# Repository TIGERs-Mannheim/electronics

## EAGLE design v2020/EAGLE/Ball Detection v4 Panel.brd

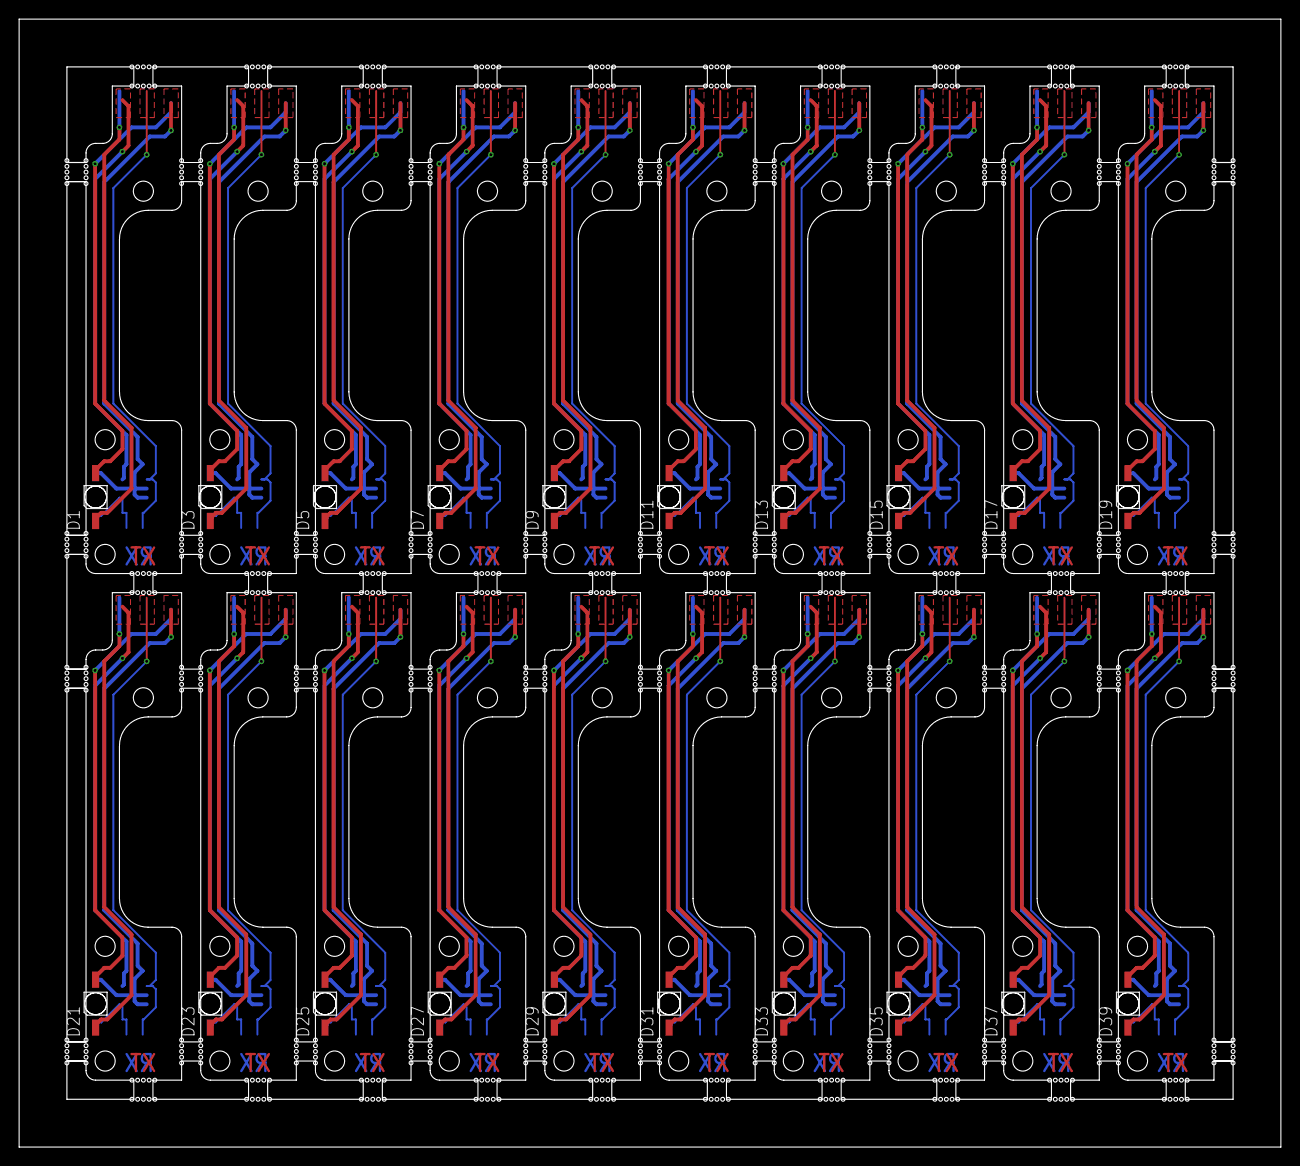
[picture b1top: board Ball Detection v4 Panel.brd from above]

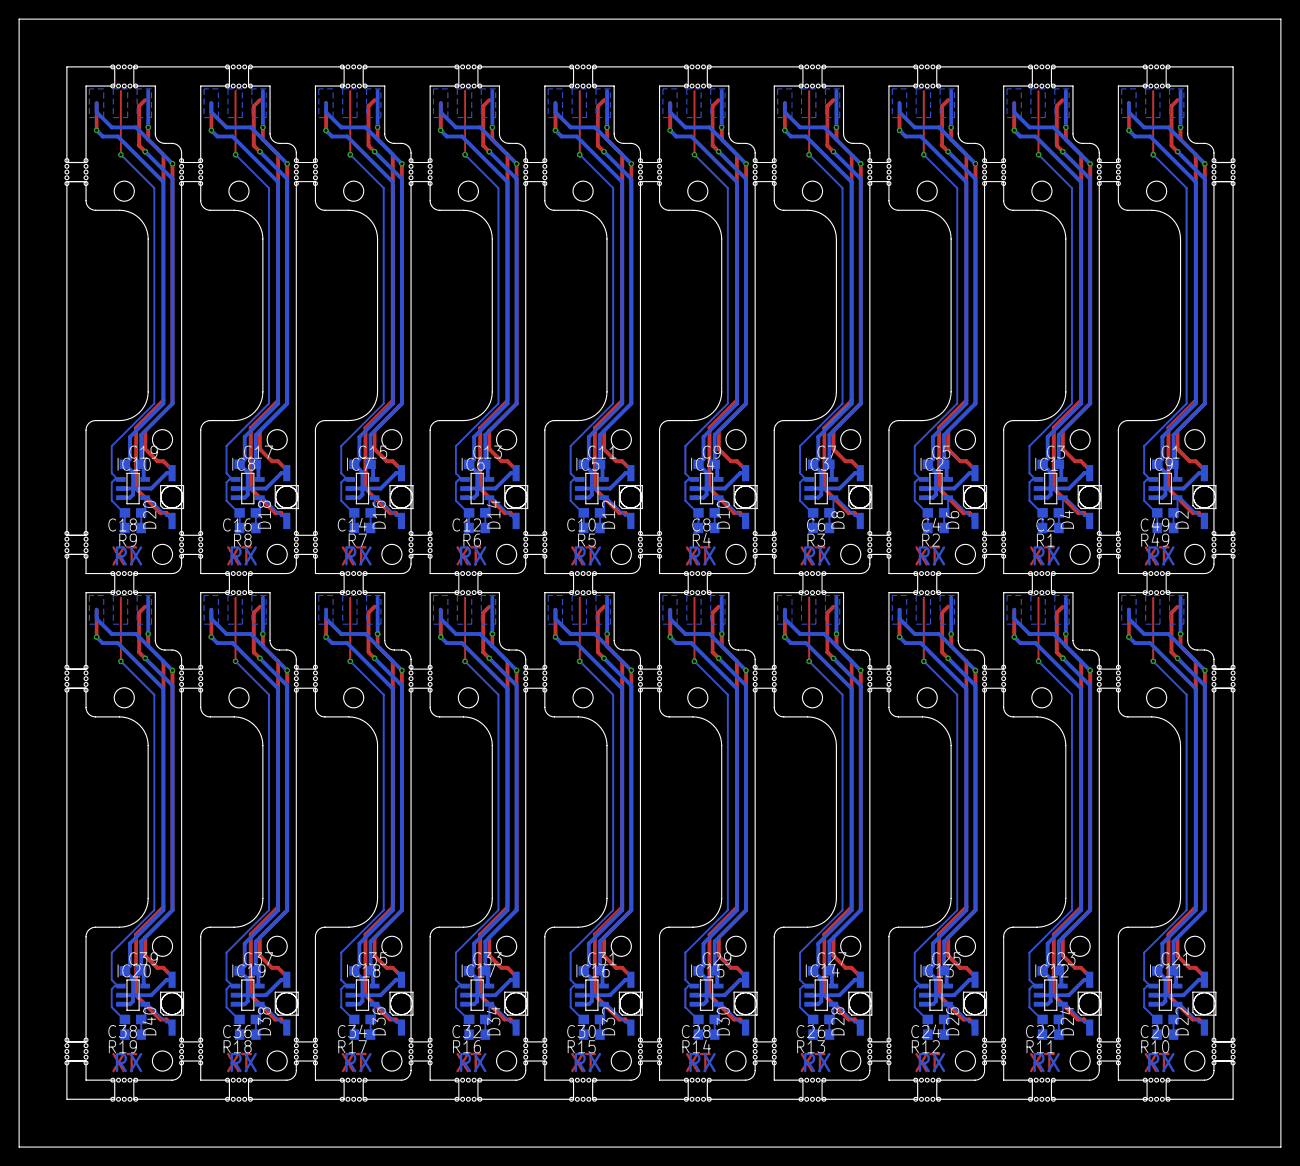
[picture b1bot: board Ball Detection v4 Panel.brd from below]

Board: 2 copper layers, 132.0 x 118.0 mm, 120 parts (100 on the bottom side), 80 nets.

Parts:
C1, C3, C5, C7, C9, C11, C13, C15, C17, C19, C21, C23, C25, C27, C29, C31, C33, C35, C37, C39: 10u; C0603
C2, C4, C6, C8, C10, C12, C14, C16, C18, C20, C22, C24, C26, C28, C30, C32, C34, C36, C38, C49: 10p; C0603
D1, D3, D5, D7, D9, D11, D13, D15, D17, D19, D21, D23, D25, D27, D29, D31, D33, D35, D37, D39: VSMB2000X01; LED-GULLR
D2, D4, D6, D8, D10, D12, D14, D16, D18, D20, D22, D24, D26, D28, D30, D32, D34, D36, D38, D40: TEMD1000; LED-GULLR
IC1, IC2, IC3, IC4, IC5, IC6, IC7, IC8, IC9, IC10, IC11, IC12, IC13, IC14, IC15, IC16, IC17, IC18, IC19, IC20: OPA320; SOT23-5
R1, R2, R3, R4, R5, R6, R7, R8, R9, R10, R11, R12, R13, R14, R15, R16, R17, R18, R19, R49: 1M; R0603

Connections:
GND: C1.1, D2.A, IC9.2, IC9.3
GND1: C3.1, D4.A, IC1.2, IC1.3
GND2: C5.1, D6.A, IC2.2, IC2.3
GND3: C7.1, D8.A, IC3.2, IC3.3
GND4: C9.1, D10.A, IC4.2, IC4.3
GND5: C11.1, D12.A, IC5.2, IC5.3
GND6: C13.1, D14.A, IC6.2, IC6.3
GND7: C15.1, D16.A, IC7.2, IC7.3
GND8: C17.1, D18.A, IC8.2, IC8.3
GND9: C19.1, D20.A, IC10.2, IC10.3
GND10: C21.1, D22.A, IC11.2, IC11.3
GND11: C23.1, D24.A, IC12.2, IC12.3
GND12: C25.1, D26.A, IC13.2, IC13.3
GND13: C27.1, D28.A, IC14.2, IC14.3
GND14: C29.1, D30.A, IC15.2, IC15.3
GND15: C31.1, D32.A, IC16.2, IC16.3
GND16: C33.1, D34.A, IC17.2, IC17.3
GND17: C35.1, D36.A, IC18.2, IC18.3
GND18: C37.1, D38.A, IC19.2, IC19.3
GND19: C39.1, D40.A, IC20.2, IC20.3
IR-ADC: C49.2, IC9.1, R49.2
IR-ADC1: C2.2, IC1.1, R1.2
IR-ADC2: C4.2, IC2.1, R2.2
IR-ADC3: C6.2, IC3.1, R3.2
IR-ADC4: C8.2, IC4.1, R4.2
IR-ADC5: C10.2, IC5.1, R5.2
IR-ADC6: C12.2, IC6.1, R6.2
IR-ADC7: C14.2, IC7.1, R7.2
IR-ADC8: C16.2, IC8.1, R8.2
IR-ADC9: C18.2, IC10.1, R9.2
IR-ADC10: C20.2, IC11.1, R10.2
IR-ADC11: C22.2, IC12.1, R11.2
IR-ADC12: C24.2, IC13.1, R12.2
IR-ADC13: C26.2, IC14.1, R13.2
IR-ADC14: C28.2, IC15.1, R14.2
IR-ADC15: C30.2, IC16.1, R15.2
IR-ADC16: C32.2, IC17.1, R16.2
IR-ADC17: C34.2, IC18.1, R17.2
IR-ADC18: C36.2, IC19.1, R18.2
IR-ADC19: C38.2, IC20.1, R19.2
unnamed: C2.1, D4.C, IC1.4, R1.1
unnamed: C4.1, D6.C, IC2.4, R2.1
unnamed: C6.1, D8.C, IC3.4, R3.1
unnamed: C8.1, D10.C, IC4.4, R4.1
unnamed: C10.1, D12.C, IC5.4, R5.1
unnamed: C12.1, D14.C, IC6.4, R6.1
unnamed: C14.1, D16.C, IC7.4, R7.1
unnamed: C16.1, D18.C, IC8.4, R8.1
unnamed: C18.1, D20.C, IC10.4, R9.1
unnamed: C20.1, D22.C, IC11.4, R10.1
unnamed: C22.1, D24.C, IC12.4, R11.1
unnamed: C24.1, D26.C, IC13.4, R12.1
unnamed: C26.1, D28.C, IC14.4, R13.1
unnamed: C28.1, D30.C, IC15.4, R14.1
unnamed: C30.1, D32.C, IC16.4, R15.1
unnamed: C32.1, D34.C, IC17.4, R16.1
unnamed: C34.1, D36.C, IC18.4, R17.1
unnamed: C36.1, D38.C, IC19.4, R18.1
unnamed: C38.1, D40.C, IC20.4, R19.1
unnamed: C49.1, D2.C, IC9.4, R49.1
RX+3V1: C3.2, IC1.5
RX+3V2: C5.2, IC2.5
RX+3V3: C1.2, IC9.5
RX+3V4: C7.2, IC3.5
RX+3V5: C9.2, IC4.5
RX+3V6: C11.2, IC5.5
RX+3V7: C13.2, IC6.5
RX+3V8: C15.2, IC7.5
RX+3V9: C17.2, IC8.5
RX+3V10: C19.2, IC10.5
RX+3V11: C21.2, IC11.5
RX+3V12: C23.2, IC12.5
RX+3V13: C25.2, IC13.5
RX+3V14: C27.2, IC14.5
RX+3V15: C29.2, IC15.5
RX+3V16: C31.2, IC16.5
RX+3V17: C33.2, IC17.5
RX+3V18: C35.2, IC18.5
RX+3V19: C37.2, IC19.5
RX+3V20: C39.2, IC20.5

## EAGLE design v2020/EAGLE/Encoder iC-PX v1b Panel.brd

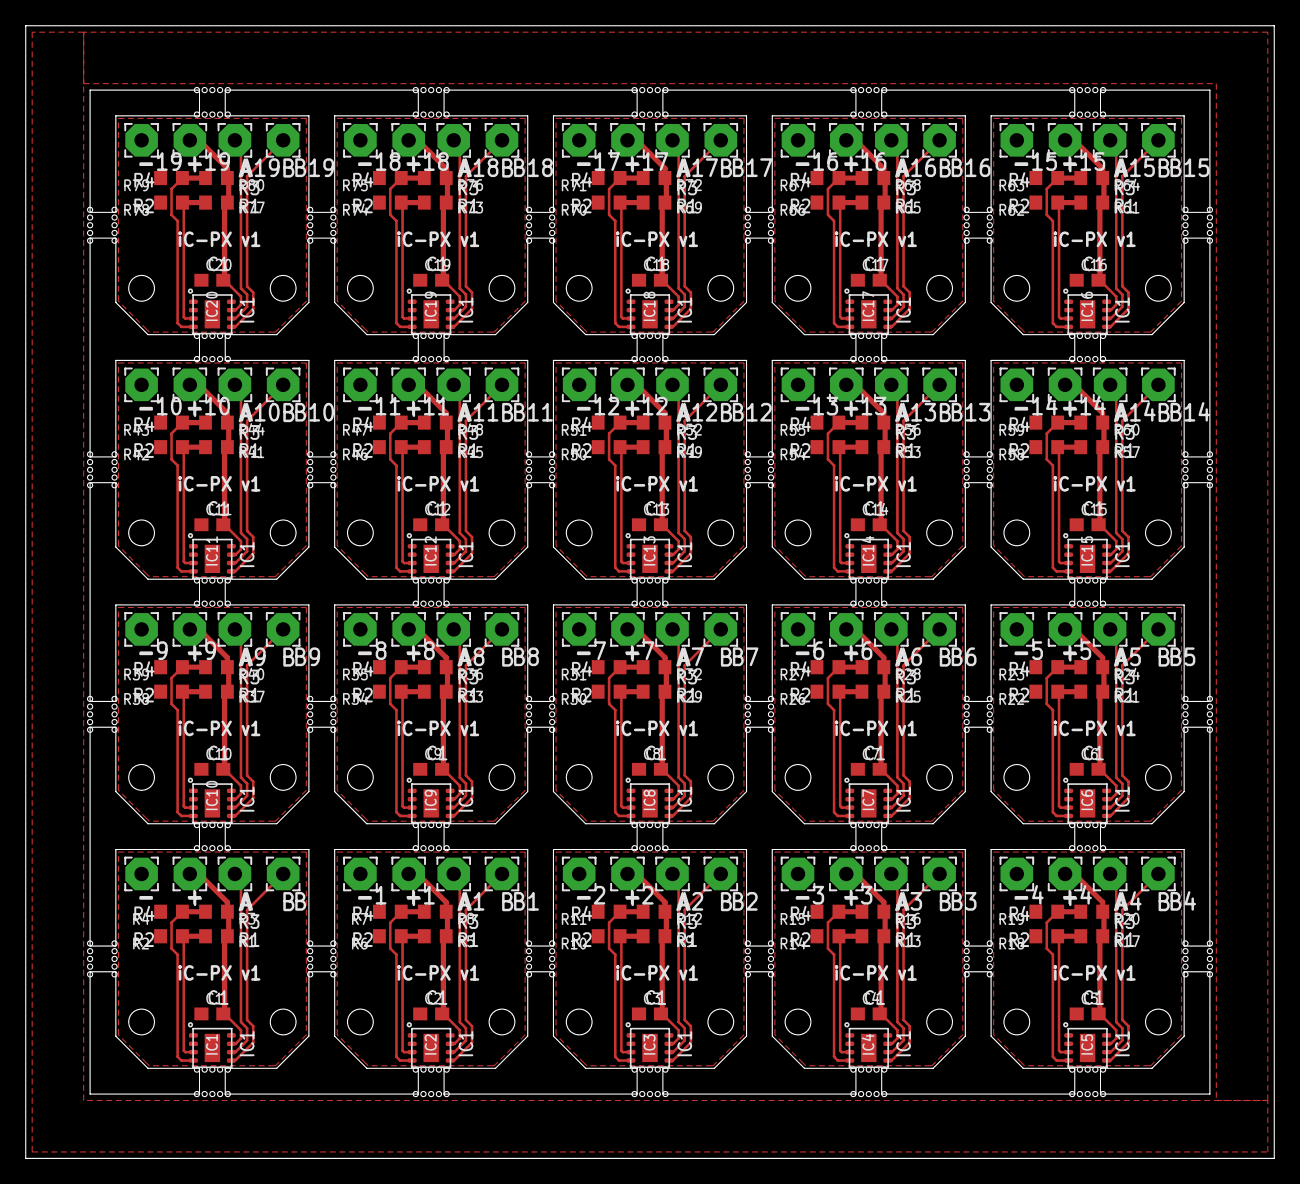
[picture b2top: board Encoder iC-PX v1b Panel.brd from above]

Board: 2 copper layers, 97.0 x 88.0 mm, 200 parts (0 on the bottom side), 120 nets.

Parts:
+, +1, +2, +3, +4, +5, +6, +7, +8, +9, +10, +11, +12, +13, +14, +15, +16, +17, +18, +19: WIREPAD2,54/1,1; 2,54/1,1
-, -1, -2, -3, -4, -5, -6, -7, -8, -9, -10, -11, -12, -13, -14, -15, -16, -17, -18, -19: WIREPAD2,54/1,1; 2,54/1,1
A, A1, A2, A3, A4, A5, A6, A7, A8, A9, A10, A11, A12, A13, A14, A15, A16, A17, A18, A19: WIREPAD2,54/1,1; 2,54/1,1
B, B1, B2, B3, B4, B5, B6, B7, B8, B9, B10, B11, B12, B13, B14, B15, B16, B17, B18, B19: WIREPAD2,54/1,1; 2,54/1,1
C1, C2, C3, C4, C5, C6, C7, C8, C9, C10, C11, C12, C13, C14, C15, C16, C17, C18, C19, C20: 100n; C0603
IC1, IC2, IC3, IC4, IC5, IC6, IC7, IC8, IC9, IC10, IC11, IC12, IC13, IC14, IC15, IC16, IC17, IC18, IC19, IC20: iC-PX2604; ODFN8-3X3
R1, R5, R9, R13, R17, R21, R25, R29, R33, R37, R41, R45, R49, R53, R57, R61, R65, R69, R73, R77: 0R; R0603
R2, R3, R4, R6, R7, R8, R10, R11, R12, R14, R15, R16, R18, R19, R20, R22, R23, R24, R26, R27, R28, R30, R31, R32, R34, R35, R36, R38, R39, R40, R42, R43, R44, R46, R47, R48, R50, R51, R52, R54, R55, R56, R58, R59, R60, R62, R63, R64, R66, R67, R68, R70, R71, R72, R74, R75, R76, R78, R79, R80: N/A; R0603

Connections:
+5V: +.1, C1.1, IC1.7, R1.2, R3.2
+5V1: +1.1, C2.1, IC2.7, R5.2, R8.2
+5V2: +2.1, C3.1, IC3.7, R9.2, R12.2
+5V3: +3.1, C4.1, IC4.7, R13.2, R16.2
+5V4: +4.1, C5.1, IC5.7, R17.2, R20.2
+5V5: +5.1, C6.1, IC6.7, R21.2, R24.2
+5V6: +6.1, C7.1, IC7.7, R25.2, R28.2
+5V7: +7.1, C8.1, IC8.7, R29.2, R32.2
+5V8: +8.1, C9.1, IC9.7, R33.2, R36.2
+5V9: +9.1, C10.1, IC10.7, R37.2, R40.2
+5V10: +10.1, C11.1, IC11.7, R41.2, R44.2
+5V11: +11.1, C12.1, IC12.7, R45.2, R48.2
+5V12: +12.1, C13.1, IC13.7, R49.2, R52.2
+5V13: +13.1, C14.1, IC14.7, R53.2, R56.2
+5V14: +14.1, C15.1, IC15.7, R57.2, R60.2
+5V15: +15.1, C16.1, IC16.7, R61.2, R64.2
+5V16: +16.1, C17.1, IC17.7, R65.2, R68.2
+5V17: +17.1, C18.1, IC18.7, R69.2, R72.2
+5V18: +18.1, C19.1, IC19.7, R73.2, R76.2
+5V19: +19.1, C20.1, IC20.7, R77.2, R80.2
CH-A: A.1, IC1.6
CH-A1: A1.1, IC2.6
CH-A2: A2.1, IC3.6
CH-A3: A3.1, IC4.6
CH-A4: A4.1, IC5.6
CH-A5: A5.1, IC6.6
CH-A6: A6.1, IC7.6
CH-A7: A7.1, IC8.6
CH-A8: A8.1, IC9.6
CH-A9: A9.1, IC10.6
CH-A10: A10.1, IC11.6
CH-A11: A11.1, IC12.6
CH-A12: A12.1, IC13.6
CH-A13: A13.1, IC14.6
CH-A14: A14.1, IC15.6
CH-A15: A15.1, IC16.6
CH-A16: A16.1, IC17.6
CH-A17: A17.1, IC18.6
CH-A18: A18.1, IC19.6
CH-A19: A19.1, IC20.6
CH-B: B.1, IC1.5
CH-B1: B1.1, IC2.5
CH-B2: B2.1, IC3.5
CH-B3: B3.1, IC4.5
CH-B4: B4.1, IC5.5
CH-B5: B5.1, IC6.5
CH-B6: B6.1, IC7.5
CH-B7: B7.1, IC8.5
CH-B8: B8.1, IC9.5
CH-B9: B9.1, IC10.5
CH-B10: B10.1, IC11.5
CH-B11: B11.1, IC12.5
CH-B12: B12.1, IC13.5
CH-B13: B13.1, IC14.5
CH-B14: B14.1, IC15.5
CH-B15: B15.1, IC16.5
CH-B16: B16.1, IC17.5
CH-B17: B17.1, IC18.5
CH-B18: B18.1, IC19.5
CH-B19: B19.1, IC20.5
GND: -.1, C1.2, IC1.1, IC1.2, IC1.8, IC1.BP, R2.1, R4.1
GND1: -1.1, C2.2, IC2.1, IC2.2, IC2.8, IC2.BP, R6.1, R7.1
GND2: -2.1, C3.2, IC3.1, IC3.2, IC3.8, IC3.BP, R10.1, R11.1
GND3: -3.1, C4.2, IC4.1, IC4.2, IC4.8, IC4.BP, R14.1, R15.1
GND4: -4.1, C5.2, IC5.1, IC5.2, IC5.8, IC5.BP, R18.1, R19.1
GND5: -5.1, C6.2, IC6.1, IC6.2, IC6.8, IC6.BP, R22.1, R23.1
GND6: -6.1, C7.2, IC7.1, IC7.2, IC7.8, IC7.BP, R26.1, R27.1
GND7: -7.1, C8.2, IC8.1, IC8.2, IC8.8, IC8.BP, R30.1, R31.1
GND8: -8.1, C9.2, IC9.1, IC9.2, IC9.8, IC9.BP, R34.1, R35.1
GND9: -9.1, C10.2, IC10.1, IC10.2, IC10.8, IC10.BP, R38.1, R39.1
GND10: -10.1, C11.2, IC11.1, IC11.2, IC11.8, IC11.BP, R42.1, R43.1
GND11: -11.1, C12.2, IC12.1, IC12.2, IC12.8, IC12.BP, R46.1, R47.1
GND12: -12.1, C13.2, IC13.1, IC13.2, IC13.8, IC13.BP, R50.1, R51.1
GND13: -13.1, C14.2, IC14.1, IC14.2, IC14.8, IC14.BP, R54.1, R55.1
GND14: -14.1, C15.2, IC15.1, IC15.2, IC15.8, IC15.BP, R58.1, R59.1
GND15: -15.1, C16.2, IC16.1, IC16.2, IC16.8, IC16.BP, R62.1, R63.1
GND16: -16.1, C17.2, IC17.1, IC17.2, IC17.8, IC17.BP, R66.1, R67.1
GND17: -17.1, C18.2, IC18.1, IC18.2, IC18.8, IC18.BP, R70.1, R71.1
GND18: -18.1, C19.2, IC19.1, IC19.2, IC19.8, IC19.BP, R74.1, R75.1
GND19: -19.1, C20.2, IC20.1, IC20.2, IC20.8, IC20.BP, R78.1, R79.1
SEL1: IC1.3, R1.1, R2.2
SEL2: IC1.4, R3.1, R4.2
SEL3: IC2.3, R5.1, R6.2
SEL4: IC2.4, R7.2, R8.1
SEL5: IC3.3, R9.1, R10.2
SEL6: IC3.4, R11.2, R12.1
SEL7: IC4.3, R13.1, R14.2
SEL8: IC4.4, R15.2, R16.1
SEL9: IC5.3, R17.1, R18.2
SEL10: IC5.4, R19.2, R20.1
SEL11: IC6.3, R21.1, R22.2
SEL12: IC6.4, R23.2, R24.1
SEL13: IC7.3, R25.1, R26.2
SEL14: IC7.4, R27.2, R28.1
SEL15: IC8.3, R29.1, R30.2
SEL16: IC8.4, R31.2, R32.1
SEL17: IC9.3, R33.1, R34.2
SEL18: IC9.4, R35.2, R36.1
SEL19: IC10.3, R37.1, R38.2
SEL20: IC10.4, R39.2, R40.1
SEL21: IC11.3, R41.1, R42.2
SEL22: IC11.4, R43.2, R44.1
SEL23: IC12.3, R45.1, R46.2
SEL24: IC12.4, R47.2, R48.1
SEL25: IC13.3, R49.1, R50.2
SEL26: IC13.4, R51.2, R52.1
SEL27: IC14.3, R53.1, R54.2
SEL28: IC14.4, R55.2, R56.1
SEL29: IC15.3, R57.1, R58.2
SEL30: IC15.4, R59.2, R60.1
SEL31: IC16.3, R61.1, R62.2
SEL32: IC16.4, R63.2, R64.1
SEL33: IC17.3, R65.1, R66.2
SEL34: IC17.4, R67.2, R68.1
SEL35: IC18.3, R69.1, R70.2
SEL36: IC18.4, R71.2, R72.1
SEL37: IC19.3, R73.1, R74.2
SEL38: IC19.4, R75.2, R76.1
SEL39: IC20.3, R77.1, R78.2
SEL40: IC20.4, R79.2, R80.1

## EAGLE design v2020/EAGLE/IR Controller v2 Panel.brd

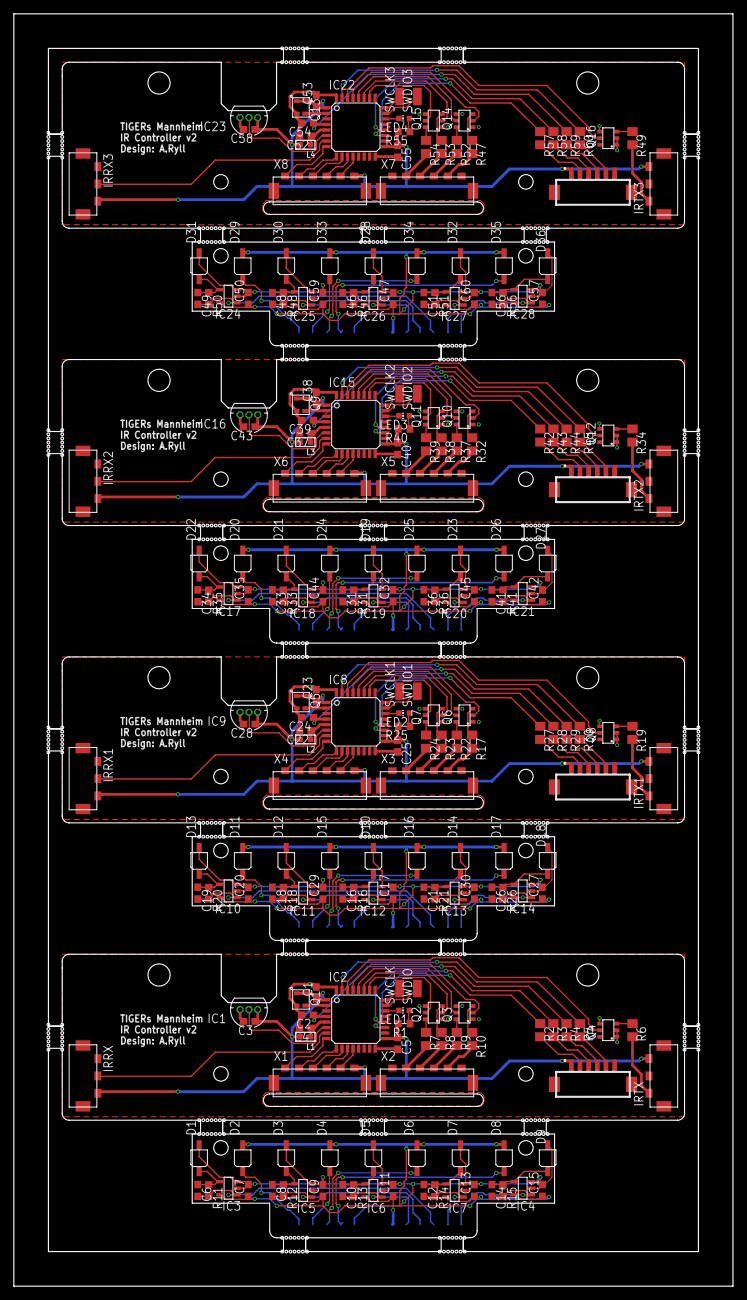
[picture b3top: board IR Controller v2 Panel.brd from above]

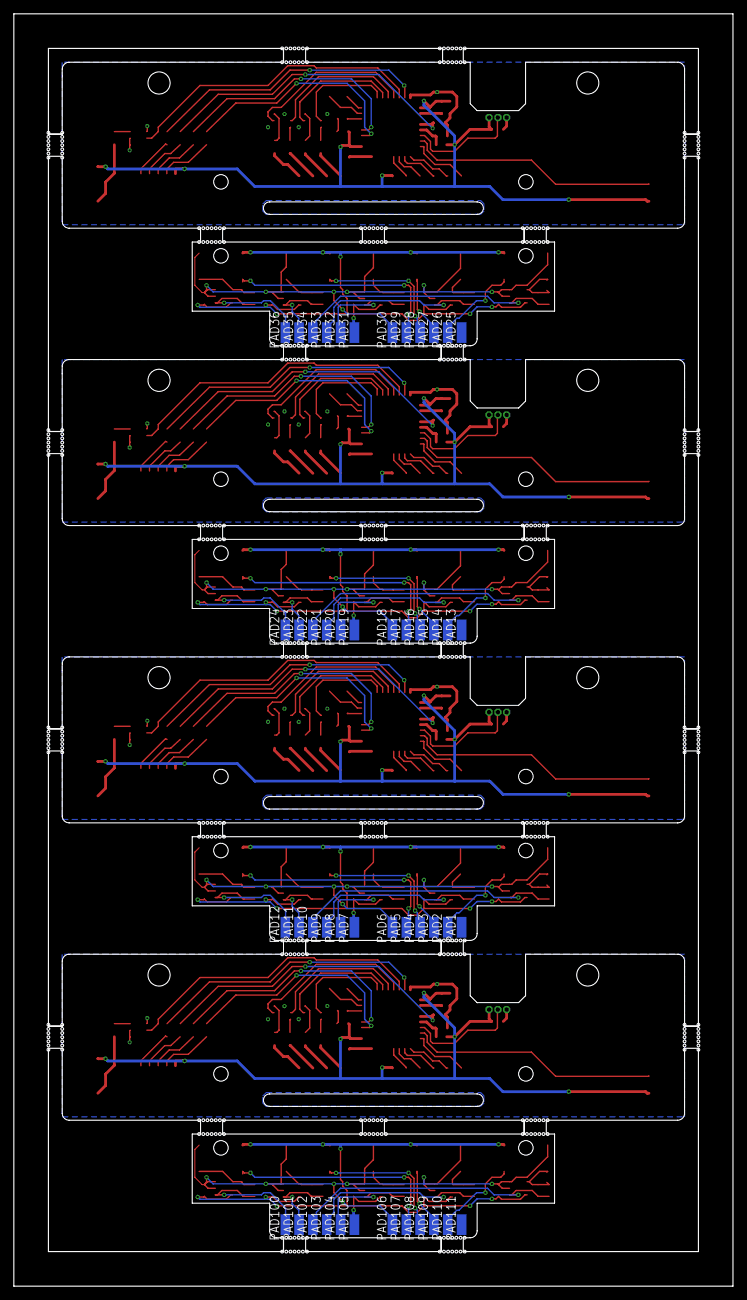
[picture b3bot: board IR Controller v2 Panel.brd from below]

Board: 2 copper layers, 104.0 x 184.0 mm, 284 parts (48 on the bottom side), 216 nets.

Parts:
C1, C2, C4, C5, C7, C9, C11, C13, C15, C17, C20, C22, C23, C24, C25, C27, C29, C30, C32, C35, C37, C38, C39, C40, C42, C44, C45, C47, C50, C52, C53, C54, C55, C57, C59, C60: 100n; C0603
C3, C28, C43, C58: 1u; C0603
C6, C8, C10, C12, C14, C16, C18, C19, C21, C26, C31, C33, C34, C36, C41, C46, C48, C49, C51, C56: 10p; C0603
D1, D3, D5, D7, D9, D10, D12, D13, D14, D18, D19, D21, D22, D23, D27, D28, D30, D31, D32, D36: TEMD1020; LED-GULL
D2, D4, D6, D8, D11, D15, D16, D17, D20, D24, D25, D26, D29, D33, D34, D35: VSMB2020X01; LED-GULL
IC1, IC9, IC16, IC23: MCP9701A; TO92
IC2, IC8, IC15, IC22: STM32F031K6T6; LQFP32-ST
IC3, IC4, IC5, IC6, IC7, IC10, IC11, IC12, IC13, IC14, IC17, IC18, IC19, IC20, IC21, IC24, IC25, IC26, IC27, IC28: OPA320; SOT23-5
IR, IR1, IR2, IR3: DF13-6P-1.25V; DF13C-6P-1.25V
IRRX, IRRX1, IRRX2, IRRX3: 009155003541006; AVX-CON3
IRTX, IRTX1, IRTX2, IRTX3: 009155003541006; AVX-CON3
L1, L2, L3, L4: 120R; L0603
LED1, LED2, LED3, LED4: gr; CHIP-LED0603
PAD1, PAD2, PAD3, PAD4, PAD5, PAD6, PAD7, PAD8, PAD9, PAD10, PAD11, PAD12, PAD13, PAD14, PAD15, PAD16, PAD17, PAD18, PAD19, PAD20, PAD21, PAD22, PAD23, PAD24, PAD25, PAD26, PAD27, PAD28, PAD29, PAD30, PAD31, PAD32, PAD33, PAD34, PAD35, PAD36, PAD100, PAD101, PAD102, PAD103, PAD104, PAD105, PAD106, PAD107, PAD108, PAD109, PAD110, PAD111: SMD1,4-3
Q1, Q5, Q9, Q13: KC2016K4.00000C1GE00; OSCI-KC2016
Q2, Q3, Q4, Q6, Q7, Q8, Q10, Q11, Q12, Q14, Q15, Q16: DMN5L06DMK-7; SOT26
R1, R25, R40, R55: 1k; R0603
R2, R3, R4, R5, R6, R7, R8, R9, R10, R17, R19, R22, R23, R24, R27, R28, R29, R30, R32, R34, R37, R38, R39, R42, R43, R44, R45, R47, R49, R52, R53, R54, R57, R58, R59, R60: 47; R0805
R11, R12, R13, R14, R15, R16, R18, R20, R21, R26, R31, R33, R35, R36, R41, R46, R48, R50, R51, R56: 1M; R0603
SWCLK, SWCLK1, SWCLK2, SWCLK3: SMD1,27-2,54
SWDIO, SWDIO1, SWDIO2, SWDIO3: SMD1,27-2,54
X1, X2, X3, X4, X5, X6, X7, X8: 00-9155-006-741-006; AVX-CON6-2MM

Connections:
+3V1: C23.1, C25.1, C28.1, IC8.1, IC8.17, IC9.3, IR1.P$1, IRRX1.1, IRTX1.1, L2.2, Q5.1, Q5.4, R25.2, X4.1
+3V2: C38.1, C40.1, C43.1, IC15.1, IC15.17, IC16.3, IR2.P$1, IRRX2.1, IRTX2.1, L3.2, Q9.1, Q9.4, R40.2, X6.1
+3V3: C1.1, C3.1, C5.1, IC1.3, IC2.1, IC2.17, IR.P$1, IRRX.1, IRTX.1, L1.2, Q1.1, Q1.4, R1.2, X1.1
+3V4: C53.1, C55.1, C58.1, IC22.1, IC22.17, IC23.3, IR3.P$1, IRRX3.1, IRTX3.1, L4.2, Q13.1, Q13.4, R55.2, X8.1
BOOT1: IC8.31, R30.1
BOOT2: IC15.31, R45.1
BOOT3: IC22.31, R60.1
BOOT5: IC2.31, R5.1
GND: C1.2, C2.2, C3.2, C4.2, C5.2, IC1.1, IC2.16, IC2.32, IR.P$6, IRRX.3, IRRX.S1, IRRX.S2, IRTX.S1, IRTX.S2, Q1.2, Q2.1, Q2.4, Q3.1, Q3.4, Q4.1, Q4.2, Q4.4, X1.S1, X1.S2, X2.6, X2.S1, X2.S2
GND1: C22.2, C23.2, C24.2, C25.2, C28.2, IC8.16, IC8.32, IC9.1, IR1.P$6, IRRX1.3, IRRX1.S1, IRRX1.S2, IRTX1.S1, IRTX1.S2, Q5.2, Q6.1, Q6.4, Q7.1, Q7.4, Q8.1, Q8.2, Q8.4, X3.6, X3.S1, X3.S2, X4.S1, X4.S2
GND2: C37.2, C38.2, C39.2, C40.2, C43.2, IC15.16, IC15.32, IC16.1, IR2.P$6, IRRX2.3, IRRX2.S1, IRRX2.S2, IRTX2.S1, IRTX2.S2, Q9.2, Q10.1, Q10.4, Q11.1, Q11.4, Q12.1, Q12.2, Q12.4, X5.6, X5.S1, X5.S2, X6.S1, X6.S2
GND3: C52.2, C53.2, C54.2, C55.2, C58.2, IC22.16, IC22.32, IC23.1, IR3.P$6, IRRX3.3, IRRX3.S1, IRRX3.S2, IRTX3.S1, IRTX3.S2, Q13.2, Q14.1, Q14.4, Q15.1, Q15.4, Q16.1, Q16.2, Q16.4, X7.6, X7.S1, X7.S2, X8.S1, X8.S2
GNDA: C7.2, C9.2, C11.2, C13.2, C15.2, D1.A, D3.A, D5.A, D7.A, D9.A, IC3.2, IC3.3, IC4.2, IC4.3, IC5.2, IC5.3, IC6.2, IC6.3, IC7.2, IC7.3, PAD106.1
GNDA1: C17.2, C20.2, C27.2, C29.2, C30.2, D10.A, D12.A, D13.A, D14.A, D18.A, IC10.2, IC10.3, IC11.2, IC11.3, IC12.2, IC12.3, IC13.2, IC13.3, IC14.2, IC14.3, PAD6.1
GNDA2: C32.2, C35.2, C42.2, C44.2, C45.2, D19.A, D21.A, D22.A, D23.A, D27.A, IC17.2, IC17.3, IC18.2, IC18.3, IC19.2, IC19.3, IC20.2, IC20.3, IC21.2, IC21.3, PAD18.1
GNDA3: C47.2, C50.2, C57.2, C59.2, C60.2, D28.A, D30.A, D31.A, D32.A, D36.A, IC24.2, IC24.3, IC25.2, IC25.3, IC26.2, IC26.3, IC27.2, IC27.3, IC28.2, IC28.3, PAD30.1
IR0: IC2.30, Q4.5
IR1: IC2.26, Q2.5
IR2: IC2.29, Q3.2
IR3: IC2.28, Q3.5
IR4: IC2.27, Q2.2
IR5: IC8.28, Q6.5
IR6: IC8.30, Q8.5
IR7: IC8.29, Q6.2
IR8: IC8.26, Q7.5
IR9: IC8.27, Q7.2
IR10: IC15.28, Q10.5
IR11: IC15.30, Q12.5
IR12: IC15.29, Q10.2
IR13: IC15.26, Q11.5
IR14: IC15.27, Q11.2
IR15: IC22.28, Q14.5
IR16: IC22.30, Q16.5
IR17: IC22.29, Q14.2
IR18: IC22.26, Q15.5
IR19: IC22.27, Q15.2
IR-ADC0: IC2.7, IRRX.2
IR-ADC1: IC2.12, X1.2
IR-ADC2: IC2.11, X1.3
IR-ADC3: IC2.10, X1.4
IR-ADC4: IC2.9, X1.5
IR-ADC5: IC2.8, X1.6
IR-ADC6: IC8.12, X4.2
IR-ADC7: IC8.7, IRRX1.2
IR-ADC8: IC8.11, X4.3
IR-ADC9: IC8.10, X4.4
IR-ADC10: IC8.9, X4.5
IR-ADC11: IC8.8, X4.6
IR-ADC12: IC15.12, X6.2
IR-ADC13: IC15.7, IRRX2.2
IR-ADC14: IC15.11, X6.3
IR-ADC15: IC15.10, X6.4
IR-ADC16: IC15.9, X6.5
IR-ADC17: IC15.8, X6.6
IR-ADC18: IC22.12, X8.2
IR-ADC19: IC22.7, IRRX3.2
IR-ADC20: IC22.11, X8.3
IR-ADC21: IC22.10, X8.4
IR-ADC22: IC22.9, X8.5
IR-ADC23: IC22.8, X8.6
IR-L1: D2.C, PAD110.1
IR-L2: D4.C, PAD109.1
IR-L3: D6.C, PAD108.1
IR-L4: D8.C, PAD107.1
IR-L5: D11.C, PAD2.1
IR-L6: D15.C, PAD3.1
IR-L7: D16.C, PAD4.1
IR-L8: D17.C, PAD5.1
IR-L9: D20.C, PAD14.1
IR-L10: D24.C, PAD15.1
IR-L11: D25.C, PAD16.1
IR-L12: D26.C, PAD17.1
IR-L13: D29.C, PAD26.1
IR-L14: D33.C, PAD27.1
IR-L15: D34.C, PAD28.1
IR-L16: D35.C, PAD29.1
IR-LED: IC2.22, LED1.C
IR-LED1: R8.2, X2.4
IR-LED2: R9.2, X2.3
IR-LED3: R10.2, X2.2
IR-LED4: R7.2, X2.5
IR-LED5: IC8.22, LED2.C
IR-LED6: R23.2, X3.4
IR-LED7: R22.2, X3.3
IR-LED8: R17.2, X3.2
IR-LED9: R24.2, X3.5
IR-LED10: IC15.22, LED3.C
IR-LED11: R38.2, X5.4
IR-LED12: R37.2, X5.3
IR-LED13: R32.2, X5.2
IR-LED14: R39.2, X5.5
IR-LED15: IC22.22, LED4.C
IR-LED16: R53.2, X7.4
IR-LED17: R52.2, X7.3
IR-LED18: R47.2, X7.2
IR-LED19: R54.2, X7.5
IR-OUT1: C6.2, IC3.1, PAD102.1, R11.2
IR-OUT2: C8.2, IC5.1, PAD103.1, R12.2
IR-OUT3: C10.2, IC6.1, PAD104.1, R13.2
IR-OUT4: C12.2, IC7.1, PAD101.1, R14.2
IR-OUT5: C14.2, IC4.1, PAD100.1, R15.2
IR-OUT6: C19.2, IC10.1, PAD10.1, R20.2
IR-OUT7: C18.2, IC11.1, PAD9.1, R18.2
IR-OUT8: C16.2, IC12.1, PAD8.1, R16.2
IR-OUT9: C21.2, IC13.1, PAD11.1, R21.2
IR-OUT10: C26.2, IC14.1, PAD12.1, R26.2
IR-OUT11: C34.2, IC17.1, PAD22.1, R35.2
IR-OUT12: C33.2, IC18.1, PAD21.1, R33.2
IR-OUT13: C31.2, IC19.1, PAD20.1, R31.2
IR-OUT14: C36.2, IC20.1, PAD23.1, R36.2
IR-OUT15: C41.2, IC21.1, PAD24.1, R41.2
IR-OUT16: C49.2, IC24.1, PAD34.1, R50.2
IR-OUT17: C48.2, IC25.1, PAD33.1, R48.2
IR-OUT18: C46.2, IC26.1, PAD32.1, R46.2
IR-OUT19: C51.2, IC27.1, PAD35.1, R51.2
IR-OUT20: C56.2, IC28.1, PAD36.1, R56.2
unnamed: IR.P$4, R4.2
unnamed: IC2.23, SWDIO.1
unnamed: C16.1, D10.C, IC12.4, R16.1
unnamed: IR.P$5, R5.2
unnamed: Q6.3, R17.1
unnamed: IC2.24, SWCLK.1
unnamed: Q8.3, R19.1
unnamed: IRTX1.3, R19.2
unnamed: C14.1, D9.C, IC4.4, R15.1
unnamed: C18.1, D12.C, IC11.4, R18.1
unnamed: C19.1, D13.C, IC10.4, R20.1
unnamed: C21.1, D14.C, IC13.4, R21.1
unnamed: Q6.6, R22.1
unnamed: Q7.3, R23.1
unnamed: Q7.6, R24.1
unnamed: C22.1, IC8.5, L2.1
unnamed: IC8.2, Q5.3
unnamed: LED2.A, R25.1
unnamed: IR1.P$4, R29.2
unnamed: IR1.P$5, R30.2
unnamed: IC8.24, SWCLK1.1
unnamed: IC8.23, SWDIO1.1
unnamed: C26.1, D18.C, IC14.4, R26.1
unnamed: C31.1, D19.C, IC19.4, R31.1
unnamed: Q10.3, R32.1
unnamed: Q12.3, R34.1
unnamed: IRTX2.3, R34.2
unnamed: C33.1, D21.C, IC18.4, R33.1
unnamed: C34.1, D22.C, IC17.4, R35.1
unnamed: C36.1, D23.C, IC20.4, R36.1
unnamed: Q10.6, R37.1
unnamed: Q11.3, R38.1
unnamed: Q11.6, R39.1
unnamed: C37.1, IC15.5, L3.1
unnamed: IC15.2, Q9.3
unnamed: LED3.A, R40.1
unnamed: IR2.P$4, R44.2
unnamed: IR2.P$5, R45.2
unnamed: IC15.24, SWCLK2.1
unnamed: IC15.23, SWDIO2.1
unnamed: C41.1, D27.C, IC21.4, R41.1
unnamed: C46.1, D28.C, IC26.4, R46.1
unnamed: Q14.3, R47.1
unnamed: Q16.3, R49.1
unnamed: IRTX3.3, R49.2
unnamed: C48.1, D30.C, IC25.4, R48.1
unnamed: C49.1, D31.C, IC24.4, R50.1
unnamed: C51.1, D32.C, IC27.4, R51.1
unnamed: Q14.6, R52.1
unnamed: Q15.3, R53.1
unnamed: C10.1, D5.C, IC6.4, R13.1
unnamed: C8.1, D3.C, IC5.4, R12.1
unnamed: Q15.6, R54.1
unnamed: C52.1, IC22.5, L4.1
unnamed: Q3.3, R10.1
unnamed: IC22.2, Q13.3
unnamed: C6.1, D1.C, IC3.4, R11.1
unnamed: LED4.A, R55.1
unnamed: IC2.2, Q1.3
unnamed: IR3.P$4, R59.2
unnamed: IR3.P$5, R60.2
unnamed: IC22.24, SWCLK3.1
unnamed: IC22.23, SWDIO3.1
unnamed: C56.1, D36.C, IC28.4, R56.1
unnamed: C4.1, IC2.5, L1.1
unnamed: IRTX.3, R6.2
unnamed: C12.1, D7.C, IC7.4, R14.1
unnamed: Q4.3, R6.1
unnamed: Q3.6, R9.1
unnamed: Q2.3, R8.1
unnamed: Q2.6, R7.1
unnamed: LED1.A, R1.1
SRST1: C24.1, IC8.4, R29.1
SRST2: C39.1, IC15.4, R44.1
SRST3: C54.1, IC22.4, R59.1
SRST5: C2.1, IC2.4, R4.1
T-ADC: IC1.2, IC2.6
T-ADC1: IC8.6, IC9.2
T-ADC2: IC15.6, IC16.2
T-ADC3: IC22.6, IC23.2
UART5-RX: IR.P$2, R2.2
UART5-RX1: IR1.P$2, R27.2
UART5-RX2: IR2.P$2, R42.2
UART5-RX3: IR3.P$2, R57.2
UART5-TX: IR.P$3, R3.2
UART5-TX1: IR1.P$3, R28.2
UART5-TX2: IR2.P$3, R43.2
UART5-TX3: IR3.P$3, R58.2
USART1-RX: IC2.20, R3.1
USART1-RX1: IC8.20, R28.1
USART1-RX2: IC15.20, R43.1
USART1-RX3: IC22.20, R58.1
USART1-TX: IC2.19, R2.1
USART1-TX1: IC8.19, R27.1
USART1-TX2: IC15.19, R42.1
USART1-TX3: IC22.19, R57.1
VCCINT: C7.1, C9.1, C11.1, C13.1, C15.1, D2.A, D4.A, D6.A, D8.A, IC3.5, IC4.5, IC5.5, IC6.5, IC7.5, PAD105.1
VCCINT1: C17.1, C20.1, C27.1, C29.1, C30.1, D11.A, D15.A, D16.A, D17.A, IC10.5, IC11.5, IC12.5, IC13.5, IC14.5, PAD7.1
VCCINT2: C32.1, C35.1, C42.1, C44.1, C45.1, D20.A, D24.A, D25.A, D26.A, IC17.5, IC18.5, IC19.5, IC20.5, IC21.5, PAD19.1
VCCINT3: C47.1, C50.1, C57.1, C59.1, C60.1, D29.A, D33.A, D34.A, D35.A, IC24.5, IC25.5, IC26.5, IC27.5, IC28.5, PAD31.1

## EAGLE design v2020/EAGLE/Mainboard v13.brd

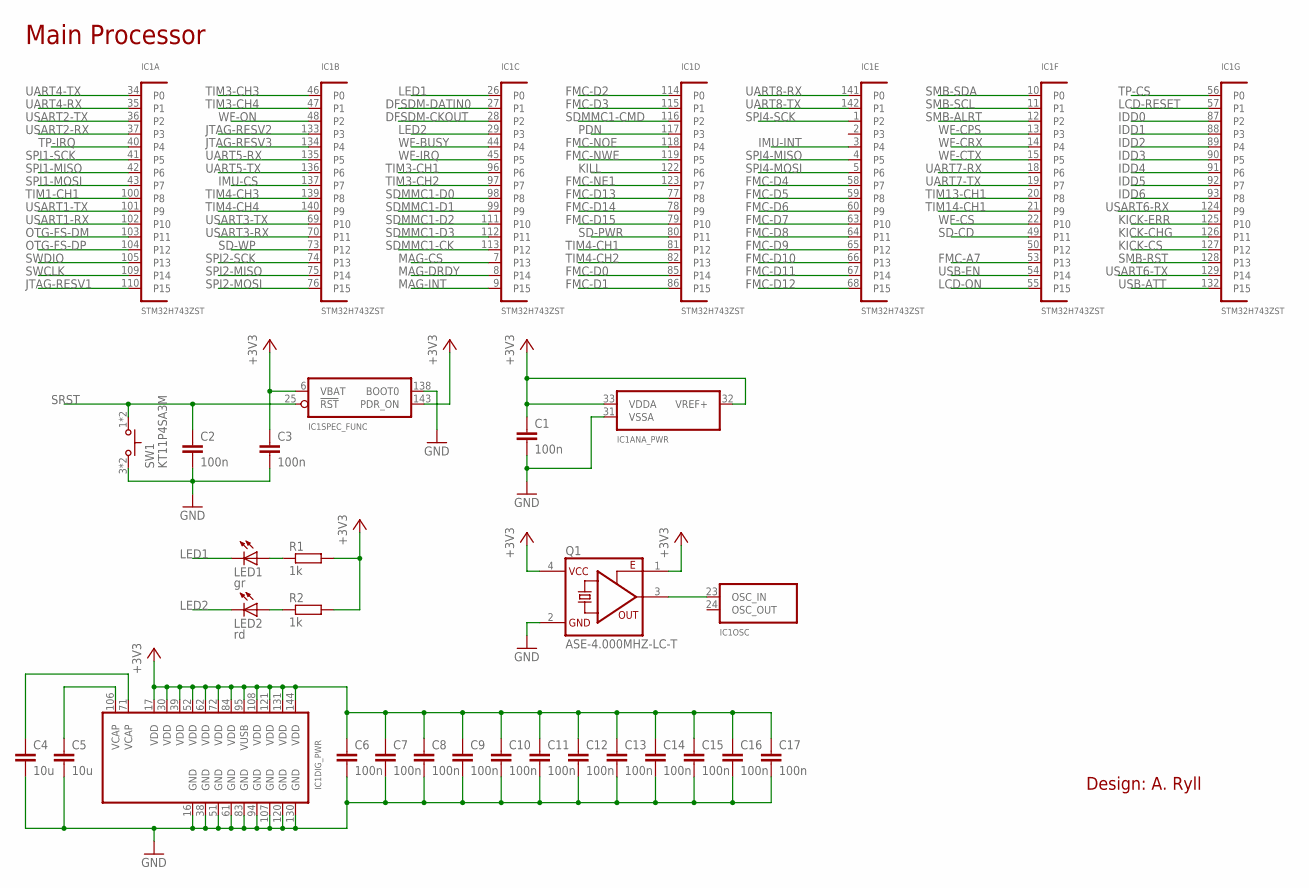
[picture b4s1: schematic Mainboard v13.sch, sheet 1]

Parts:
C1, C2, C3, C6, C7, C8, C9, C10, C11, C12, C13, C14, C15, C16, C17: 100n; C0603
C4, C5: 10u; C0603
IC1: STM32H743ZST; LQFP144-ST
LED1: gr; CHIP-LED0603
LED2: rd; CHIP-LED0603
Q1: ASE-4.000MHZ-LC-T; OSCI-ASE
R1, R2: 1k; R0603
SW1: KT11P4SA3M; BUTTON4

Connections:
+3V3: C1.1, C3.1, C6.1, C7.1, C8.1, C9.1, C10.1, C11.1, C12.1, C13.1, C14.1, C15.1, C16.1, C17.1, IC1.6 (VBAT), IC1.17 (VDD), IC1.30 (VDD), IC1.32 (VREF+), IC1.33 (VDDA), IC1.39 (VDD), IC1.52 (VDD), IC1.62 (VDD), IC1.72 (VDD), IC1.84 (VDD), IC1.95 (VUSB), IC1.108 (VDD), IC1.121 (VDD), IC1.131 (VDD), IC1.143 (PDR_ON), IC1.144 (VDD), Q1.1 (OE), Q1.4 (VCC), R1.2, R2.2; also elsewhere on the board
DFSDM-CKOUT: IC1.28 (P2); also elsewhere on the board
DFSDM-DATIN0: IC1.27 (P1); also elsewhere on the board
FMC-A7: IC1.53 (P13); also elsewhere on the board
FMC-D0: IC1.85 (P14); also elsewhere on the board
FMC-D1: IC1.86 (P15); also elsewhere on the board
FMC-D2: IC1.114 (P0); also elsewhere on the board
FMC-D3: IC1.115 (P1); also elsewhere on the board
FMC-D4: IC1.58 (P7); also elsewhere on the board
FMC-D5: IC1.59 (P8); also elsewhere on the board
FMC-D6: IC1.60 (P9); also elsewhere on the board
FMC-D7: IC1.63 (P10); also elsewhere on the board
FMC-D8: IC1.64 (P11); also elsewhere on the board
FMC-D9: IC1.65 (P12); also elsewhere on the board
FMC-D10: IC1.66 (P13); also elsewhere on the board
FMC-D11: IC1.67 (P14); also elsewhere on the board
FMC-D12: IC1.68 (P15); also elsewhere on the board
FMC-D13: IC1.77 (P8); also elsewhere on the board
FMC-D14: IC1.78 (P9); also elsewhere on the board
FMC-D15: IC1.79 (P10); also elsewhere on the board
FMC-NE1: IC1.123 (P7); also elsewhere on the board
FMC-NOE: IC1.118 (P4); also elsewhere on the board
FMC-NWE: IC1.119 (P5); also elsewhere on the board
GND: C1.2, C2.2, C3.2, C4.2, C5.2, C6.2, C7.2, C8.2, C9.2, C10.2, C11.2, C12.2, C13.2, C14.2, C15.2, C16.2, C17.2, IC1.16 (GND), IC1.31 (VSSA), IC1.38 (GND), IC1.51 (GND), IC1.61 (GND), IC1.83 (GND), IC1.94 (GND), IC1.107 (GND), IC1.120 (GND), IC1.130 (GND), IC1.138 (BOOT0), Q1.2 (GND), SW1.3 (2), SW1.4 (2); also elsewhere on the board
IDD0: IC1.87 (P2); also elsewhere on the board
IDD1: IC1.88 (P3); also elsewhere on the board
IDD2: IC1.89 (P4); also elsewhere on the board
IDD3: IC1.90 (P5); also elsewhere on the board
IDD4: IC1.91 (P6); also elsewhere on the board
IDD5: IC1.92 (P7); also elsewhere on the board
IDD6: IC1.93 (P8); also elsewhere on the board
IMU-CS: IC1.137 (P7); also elsewhere on the board
IMU-INT: IC1.3 (P4); also elsewhere on the board
JTAG-RESV1: IC1.110 (P15)
JTAG-RESV2: IC1.133 (P3)
JTAG-RESV3: IC1.134 (P4)
KICK-CHG: IC1.126 (P11); also elsewhere on the board
KICK-CS: IC1.127 (P12); also elsewhere on the board
KICK-ERR: IC1.125 (P10); also elsewhere on the board
KILL: IC1.122 (P6); also elsewhere on the board
LCD-ON: IC1.55 (P15); also elsewhere on the board
LCD-RESET: IC1.57 (P1); also elsewhere on the board
LED1: IC1.26 (P0), LED1.C
LED2: IC1.29 (P3), LED2.C
MAG-CS: IC1.7 (P13); also elsewhere on the board
MAG-DRDY: IC1.8 (P14); also elsewhere on the board
MAG-INT: IC1.9 (P15); also elsewhere on the board
unnamed: LED1.A, R1.1
unnamed: LED2.A, R2.1
unnamed: IC1.23 (OSC_IN), Q1.3 (FO)
unnamed: C5.1, IC1.106 (VCAP)
unnamed: C4.1, IC1.71 (VCAP)
OTG-FS-DM: IC1.103 (P11); also elsewhere on the board
OTG-FS-DP: IC1.104 (P12); also elsewhere on the board
PDN: IC1.117 (P3); also elsewhere on the board
SD-CD: IC1.49 (P11); also elsewhere on the board
SD-PWR: IC1.80 (P11); also elsewhere on the board
SD-WP: IC1.73 (P12); also elsewhere on the board
SDMMC1-CK: IC1.113 (P12); also elsewhere on the board
SDMMC1-CMD: IC1.116 (P2); also elsewhere on the board
SDMMC1-D0: IC1.98 (P8); also elsewhere on the board
SDMMC1-D1: IC1.99 (P9); also elsewhere on the board
SDMMC1-D2: IC1.111 (P10); also elsewhere on the board
SDMMC1-D3: IC1.112 (P11); also elsewhere on the board
SMB-ALRT: IC1.12 (P2); also elsewhere on the board
SMB-RST: IC1.128 (P13); also elsewhere on the board
SMB-SCL: IC1.11 (P1); also elsewhere on the board
SMB-SDA: IC1.10 (P0); also elsewhere on the board
SPI1-MISO: IC1.42 (P6); also elsewhere on the board
SPI1-MOSI: IC1.43 (P7); also elsewhere on the board
SPI1-SCK: IC1.41 (P5); also elsewhere on the board
SPI2-MISO: IC1.75 (P14); also elsewhere on the board
SPI2-MOSI: IC1.76 (P15); also elsewhere on the board
SPI2-SCK: IC1.74 (P13); also elsewhere on the board
SPI4-MISO: IC1.4 (P5); also elsewhere on the board
SPI4-MOSI: IC1.5 (P6); also elsewhere on the board
SPI4-SCK: IC1.1 (P2); also elsewhere on the board
SRST: C2.1, IC1.25 (!RST), SW1.1, SW1.2 (1); also elsewhere on the board
SWCLK: IC1.109 (P14); also elsewhere on the board
SWDIO: IC1.105 (P13); also elsewhere on the board
TIM1-CH1: IC1.100 (P8); also elsewhere on the board
TIM3-CH1: IC1.96 (P6); also elsewhere on the board
TIM3-CH2: IC1.97 (P7); also elsewhere on the board
TIM3-CH3: IC1.46 (P0); also elsewhere on the board
TIM3-CH4: IC1.47 (P1); also elsewhere on the board
TIM4-CH1: IC1.81 (P12); also elsewhere on the board
TIM4-CH2: IC1.82 (P13); also elsewhere on the board
TIM4-CH3: IC1.139 (P8); also elsewhere on the board
TIM4-CH4: IC1.140 (P9); also elsewhere on the board
TIM13-CH1: IC1.20 (P8); also elsewhere on the board
TIM14-CH1: IC1.21 (P9); also elsewhere on the board
TP-CS: IC1.56 (P0); also elsewhere on the board
TP-IRQ: IC1.40 (P4); also elsewhere on the board
UART4-RX: IC1.35 (P1); also elsewhere on the board
UART4-TX: IC1.34 (P0); also elsewhere on the board
UART5-RX: IC1.135 (P5); also elsewhere on the board
UART5-TX: IC1.136 (P6); also elsewhere on the board
UART7-RX: IC1.18 (P6); also elsewhere on the board
UART7-TX: IC1.19 (P7); also elsewhere on the board
UART8-RX: IC1.141 (P0); also elsewhere on the board
UART8-TX: IC1.142 (P1); also elsewhere on the board
USART1-RX: IC1.102 (P10); also elsewhere on the board
USART1-TX: IC1.101 (P9); also elsewhere on the board
USART2-RX: IC1.37 (P3); also elsewhere on the board
USART2-TX: IC1.36 (P2); also elsewhere on the board
USART3-RX: IC1.70 (P11); also elsewhere on the board
USART3-TX: IC1.69 (P10); also elsewhere on the board
USART6-RX: IC1.124 (P9); also elsewhere on the board
USART6-TX: IC1.129 (P14); also elsewhere on the board
USB-ATT: IC1.132 (P15); also elsewhere on the board
USB-EN: IC1.54 (P14); also elsewhere on the board
WF-BUSY: IC1.44 (P4); also elsewhere on the board
WF-CPS: IC1.13 (P3); also elsewhere on the board
WF-CRX: IC1.14 (P4); also elsewhere on the board
WF-CS: IC1.22 (P10); also elsewhere on the board
WF-CTX: IC1.15 (P5); also elsewhere on the board
WF-IRQ: IC1.45 (P5); also elsewhere on the board
WF-ON: IC1.48 (P2); also elsewhere on the board

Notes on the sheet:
Design: A. Ryll
Main Processor

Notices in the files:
parts and their libraries:
rc-master-smd: Copyright (C) 2007, Bob Starr
